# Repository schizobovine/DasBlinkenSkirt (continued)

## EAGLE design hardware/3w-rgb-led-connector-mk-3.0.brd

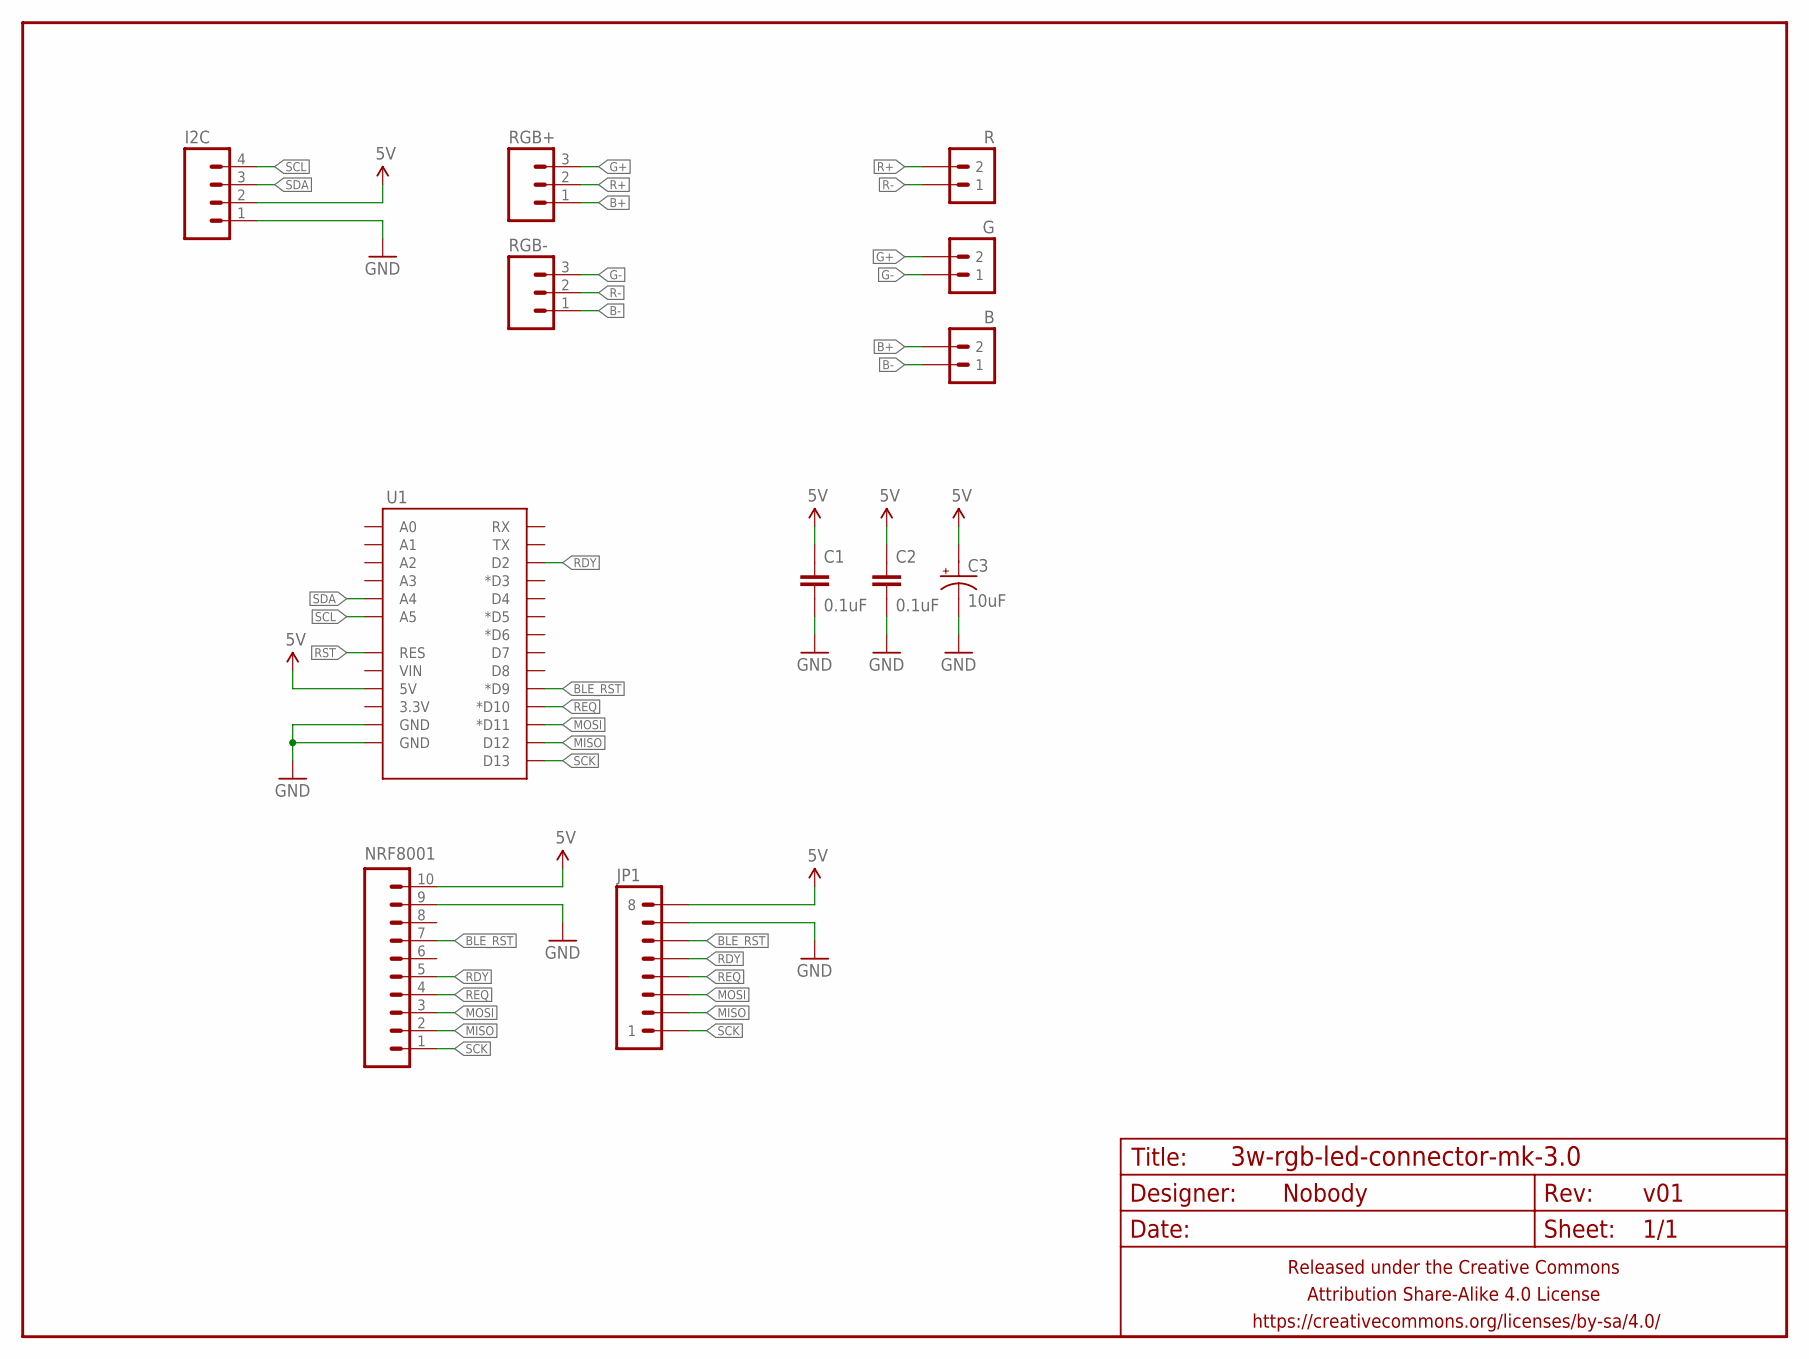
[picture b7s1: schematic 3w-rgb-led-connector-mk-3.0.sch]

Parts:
B: M023.5MM-NO_SILK; SCREWTERMINAL-3.5MM-2-NS
C1, C2: 0.1uF; C025-024X044
C3: 10uF; E2-5
FRAME1: FRAME-LETTERNO_PACKAGE; DUMMY
G: M023.5MM-NO_SILK; SCREWTERMINAL-3.5MM-2-NS
I2C: M04JST-PTH; JST-4-PH-RA-PTH
JP1: M081X08; 1X08
NRF8001: M10PTH-SLIM-ASS; 1X10_PTH_SLIMASS
R: M023.5MM-NO_SILK; SCREWTERMINAL-3.5MM-2-NS
RGB+: M03JST-XH-RA-PTH; JST-3-XH-RA-PTH
RGB-: M03JST-XH-RA-PTH; JST-3-XH-RA-PTH
U1: ARDUINO_SHIELD_SMALLER; ARDUINO_SHIELD_NOOUTLINE_INSIDE_SMALLER

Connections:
5V: C1.1, C2.1, C3.+, I2C.2, JP1.8, NRF8001.10, U1.5V
B+: B.2, RGB+.1
B-: B.1, RGB-.1
BLE_RST: JP1.6, NRF8001.7, U1.D9 (*D9)
G+: G.2, RGB+.3
G-: G.1, RGB-.3
GND: C1.2, C2.2, C3.-, I2C.1, JP1.7, NRF8001.9, U1.GND@0 (GND), U1.GND@1 (GND)
MISO: JP1.2, NRF8001.2, U1.D12
MOSI: JP1.3, NRF8001.3, U1.D11 (*D11)
R+: R.2, RGB+.2
R-: R.1, RGB-.2
RDY: JP1.5, NRF8001.5, U1.D2
REQ: JP1.4, NRF8001.4, U1.D10 (*D10)
RST: U1.RES
SCK: JP1.1, NRF8001.1, U1.D13
SCL: I2C.4, U1.A5
SDA: I2C.3, U1.A4

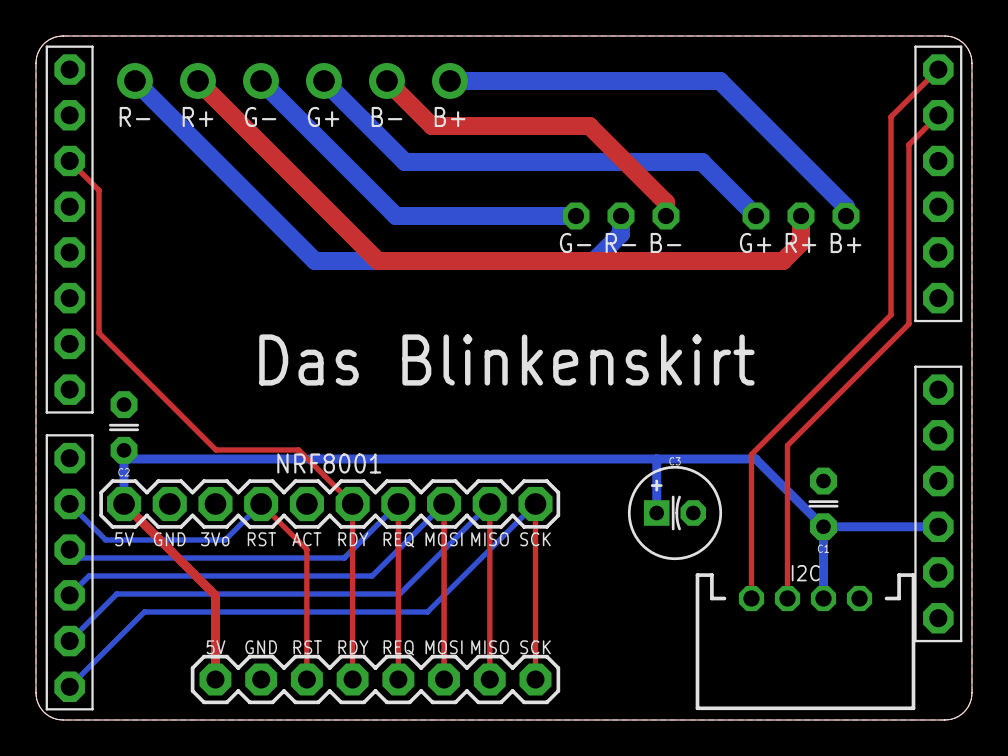
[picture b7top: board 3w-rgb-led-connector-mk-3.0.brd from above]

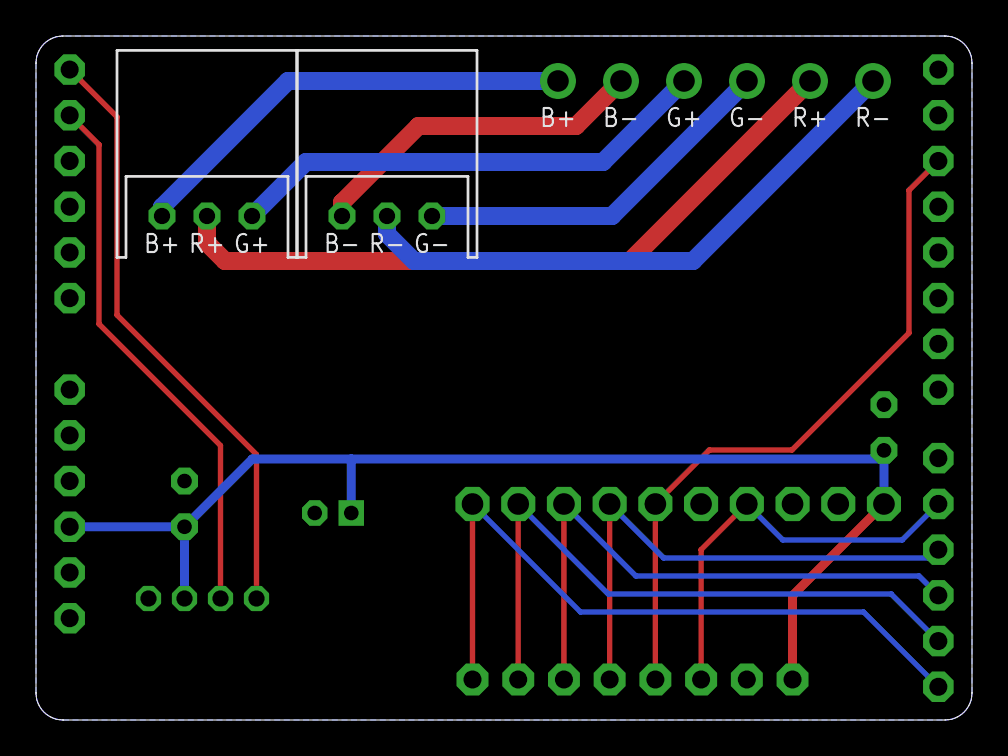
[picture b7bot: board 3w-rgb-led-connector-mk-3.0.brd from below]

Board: 2 copper layers, 52.0 x 38.0 mm, 13 parts (5 on the bottom side), 16 nets.

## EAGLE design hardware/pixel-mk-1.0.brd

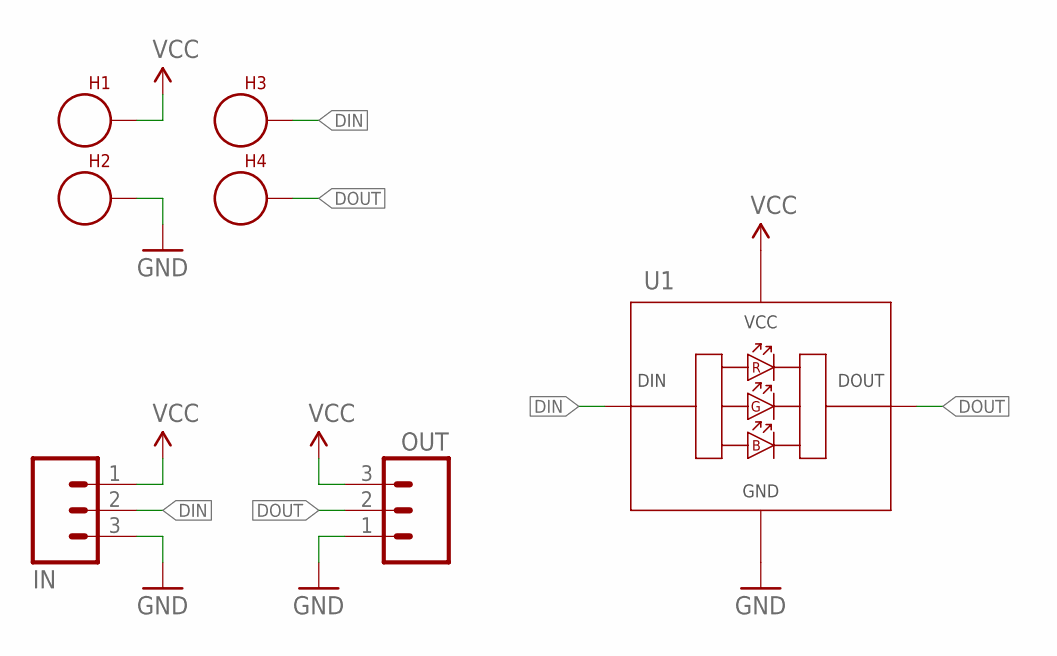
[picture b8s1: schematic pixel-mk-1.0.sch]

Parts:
H1, H2, H3, H4: SEW_HOLE; SIMPLE_HOLE
IN: M03JST-PTH; JST-3-PH-RA-PTH
OUT: M03JST-PTH; JST-3-PH-RA-PTH
U1: NEOPIXEL5MM-PTH-RA-NS; LED-5MM-PTH-FUCK-RA-NS

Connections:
DIN: H3.P$1, IN.2, U1.1 (DIN)
DOUT: H4.P$1, OUT.2, U1.4 (DOUT)
GND: H2.P$1, IN.3, OUT.1, U1.3 (GND)
VCC: H1.P$1, IN.1, OUT.3, U1.2 (VCC)

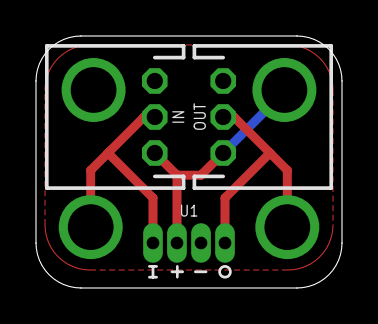
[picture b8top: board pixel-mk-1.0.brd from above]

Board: 2 copper layers, 17.0 x 14.0 mm, 7 parts (0 on the bottom side), 4 nets.

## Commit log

2015-04-19 initial checking of code, licenses and such
2015-04-20 das committen
2015-04-25 more dicking around with testing code
2015-04-27 converting adapter into a full shield so I can throw a BLE adapater for control at it
2015-04-27 enable driver by default now that i'm more sure it will work :P
2015-05-07 teehee dongle
2015-06-22 yet another connector board
2016-11-08 dotstarstick
